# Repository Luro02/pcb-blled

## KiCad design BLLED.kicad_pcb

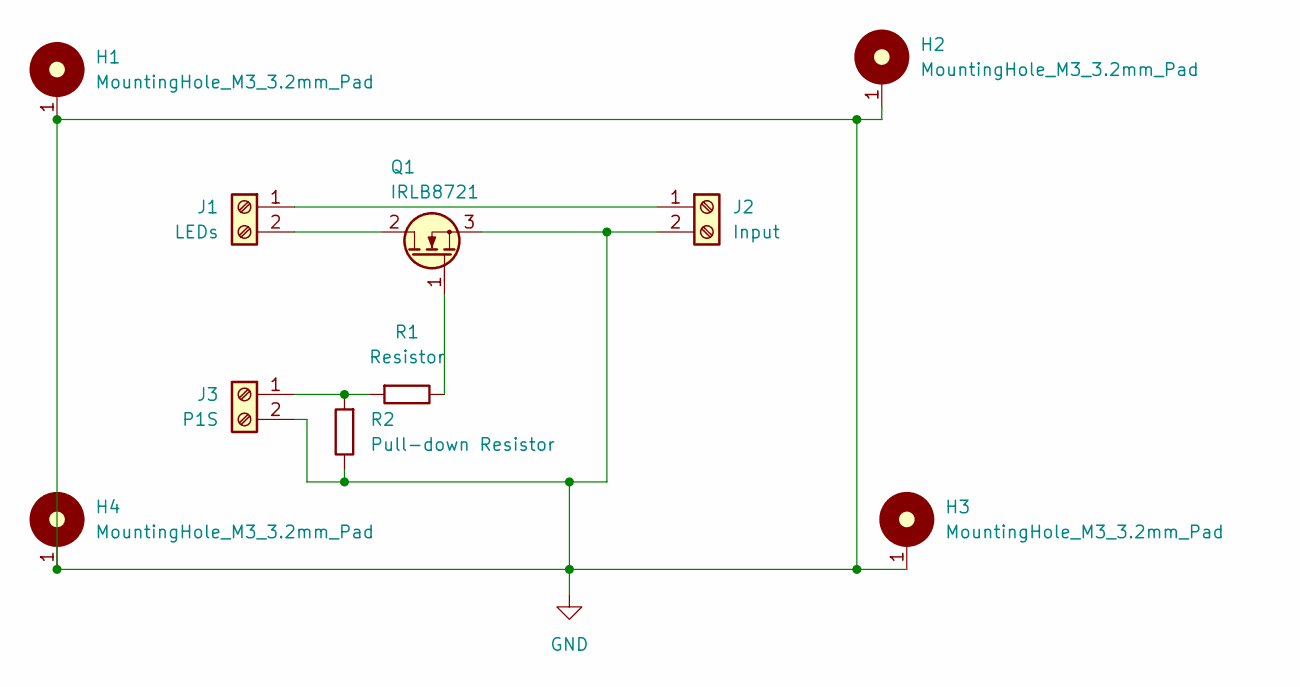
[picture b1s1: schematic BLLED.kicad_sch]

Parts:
H1, H2, H3, H4: MountingHole_M3_3.2mm_Pad; MountingHole_3.2mm_Pad
J1: LEDs; TerminalBlock_bornier-2_P5.08mm
J2: Input; TerminalBlock_bornier-2_P5.08mm
J3: P1S; TerminalBlock_bornier-2_P5.08mm
Q1: IRLB8721; TO-220-3_Horizontal_TabDown
R1: Resistor; R_Axial_DIN0207_L6.3mm_D2.5mm_P10.16mm_Horizontal
R2: Pull-down Resistor; R_Axial_DIN0207_L6.3mm_D2.5mm_P10.16mm_Horizontal

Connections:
GND: H1.1, H2.1, H3.1, H4.1, J2.2, J3.2, Q1.3 (S), R2.2
unnamed: J1.1, J2.1
unnamed: J1.2, Q1.2 (D)
unnamed: J3.1, R1.1, R2.1
unnamed: Q1.1 (G), R1.2

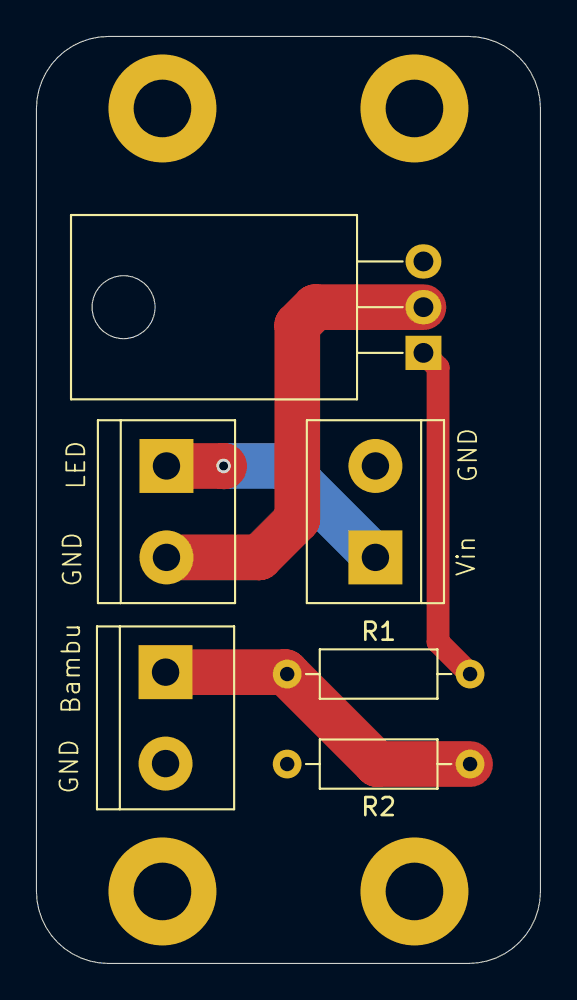
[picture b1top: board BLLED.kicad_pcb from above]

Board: 2 copper layers, 28.0 x 51.5 mm, 10 parts (0 on the bottom side), 5 nets.

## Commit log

2024-08-10 add github action
2024-08-10 update pcb
2024-08-10 add pcm symbols
